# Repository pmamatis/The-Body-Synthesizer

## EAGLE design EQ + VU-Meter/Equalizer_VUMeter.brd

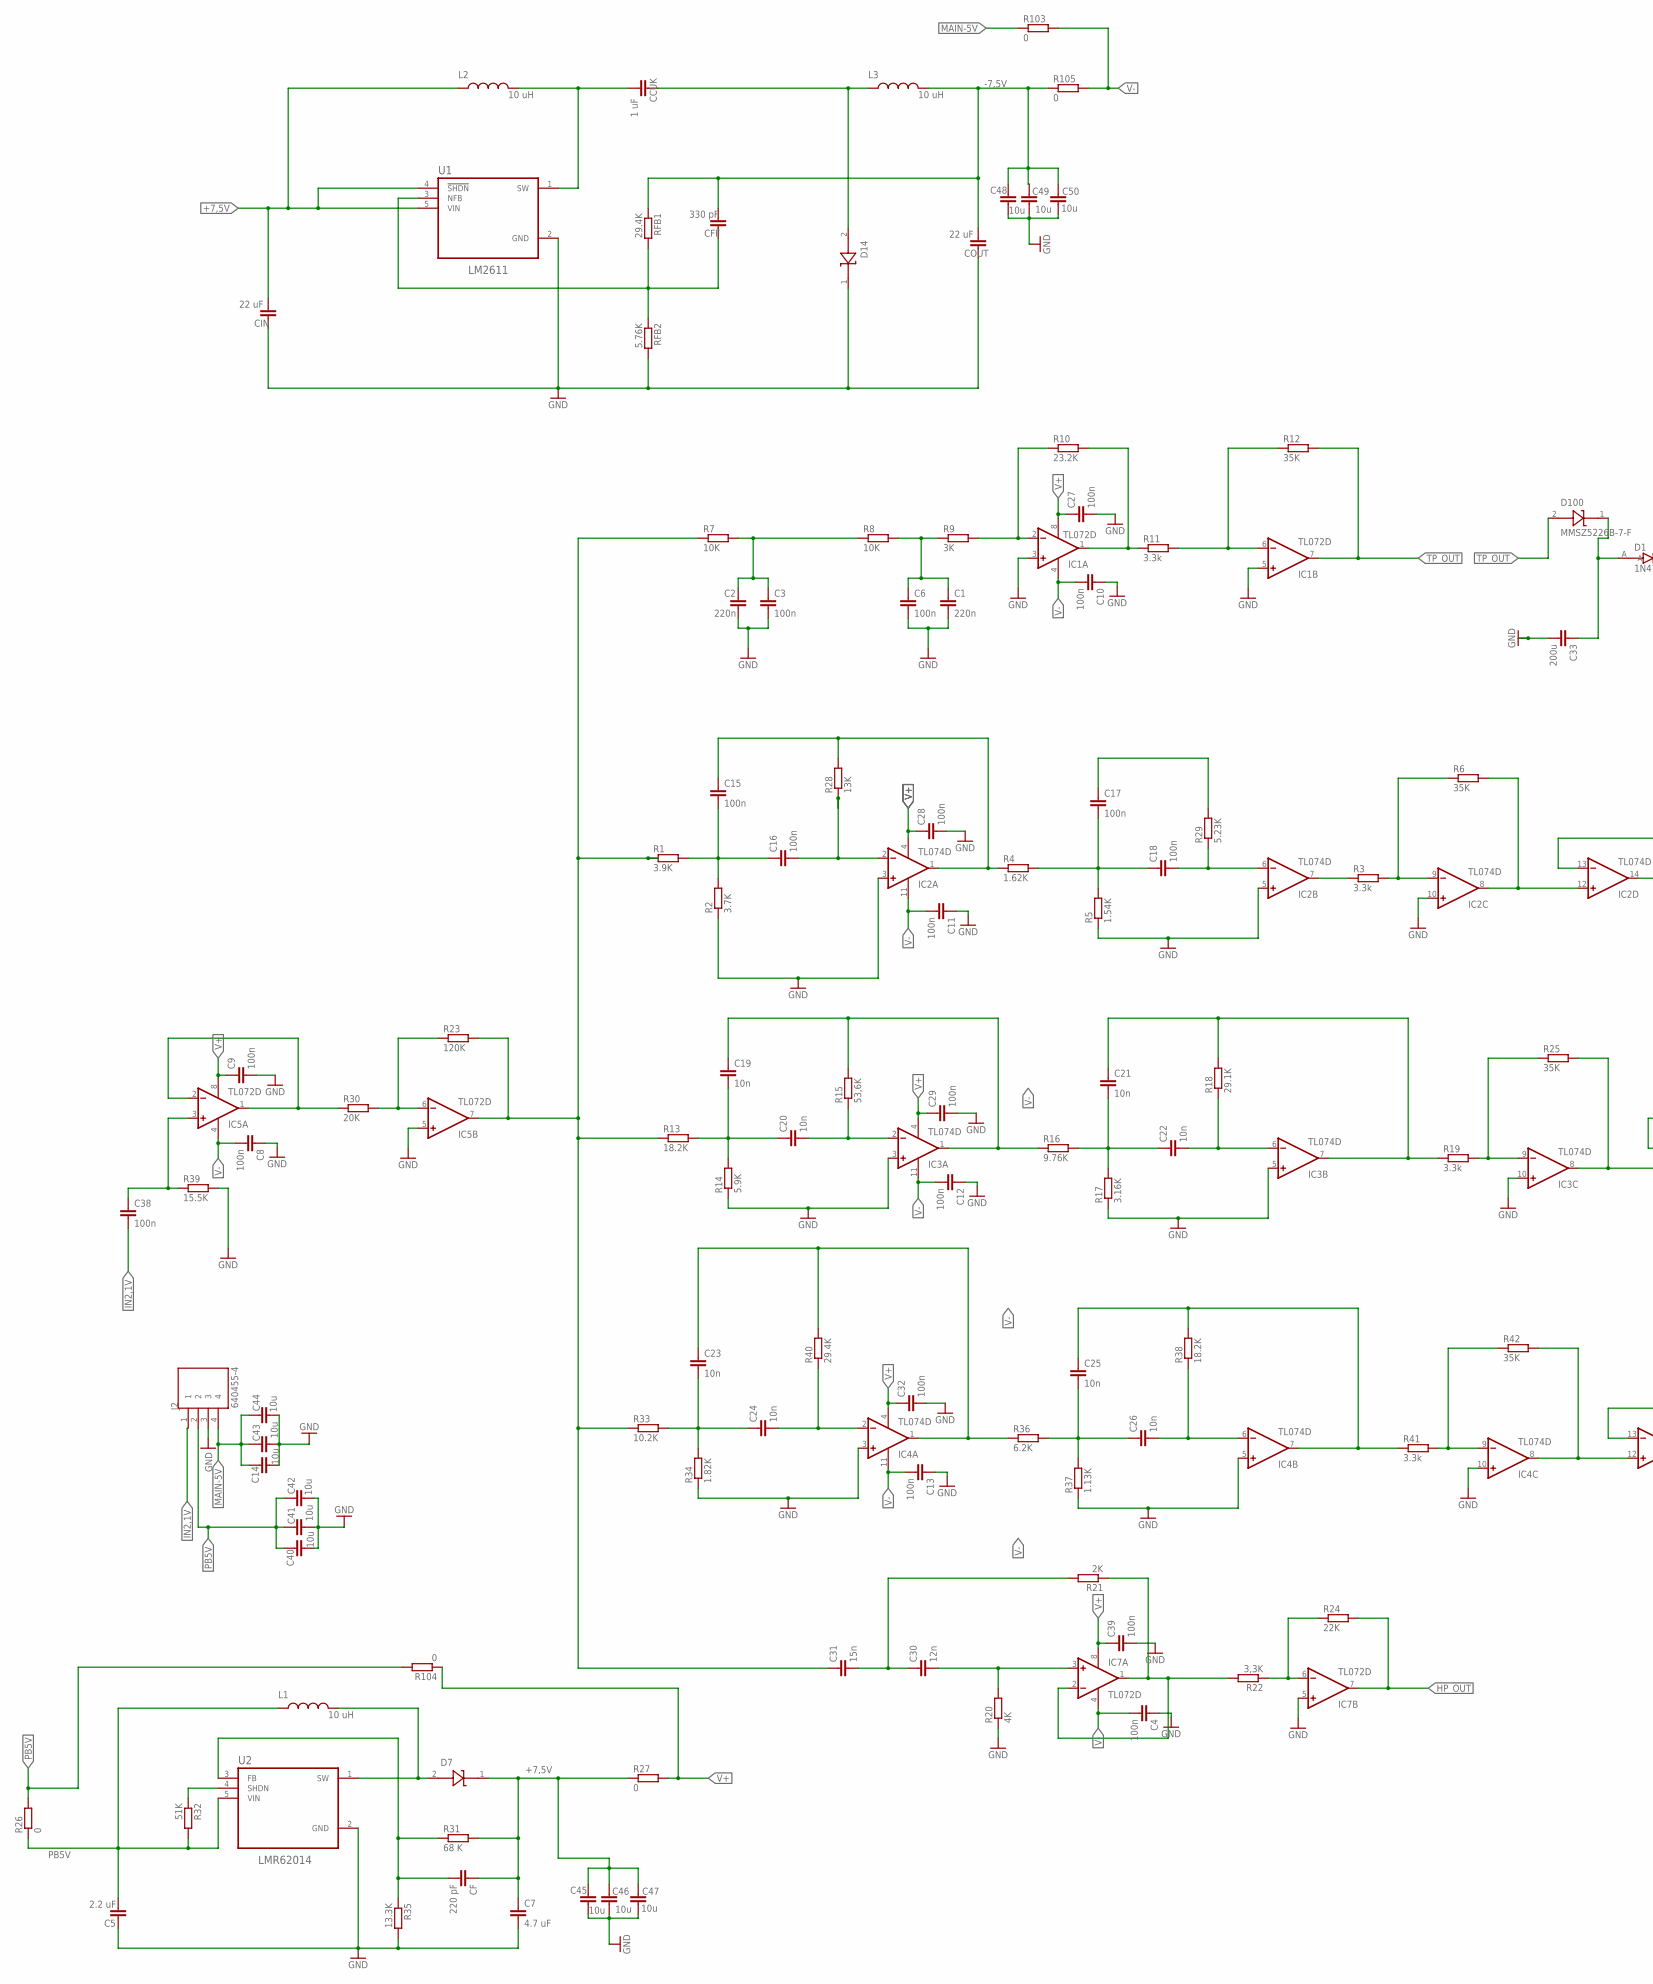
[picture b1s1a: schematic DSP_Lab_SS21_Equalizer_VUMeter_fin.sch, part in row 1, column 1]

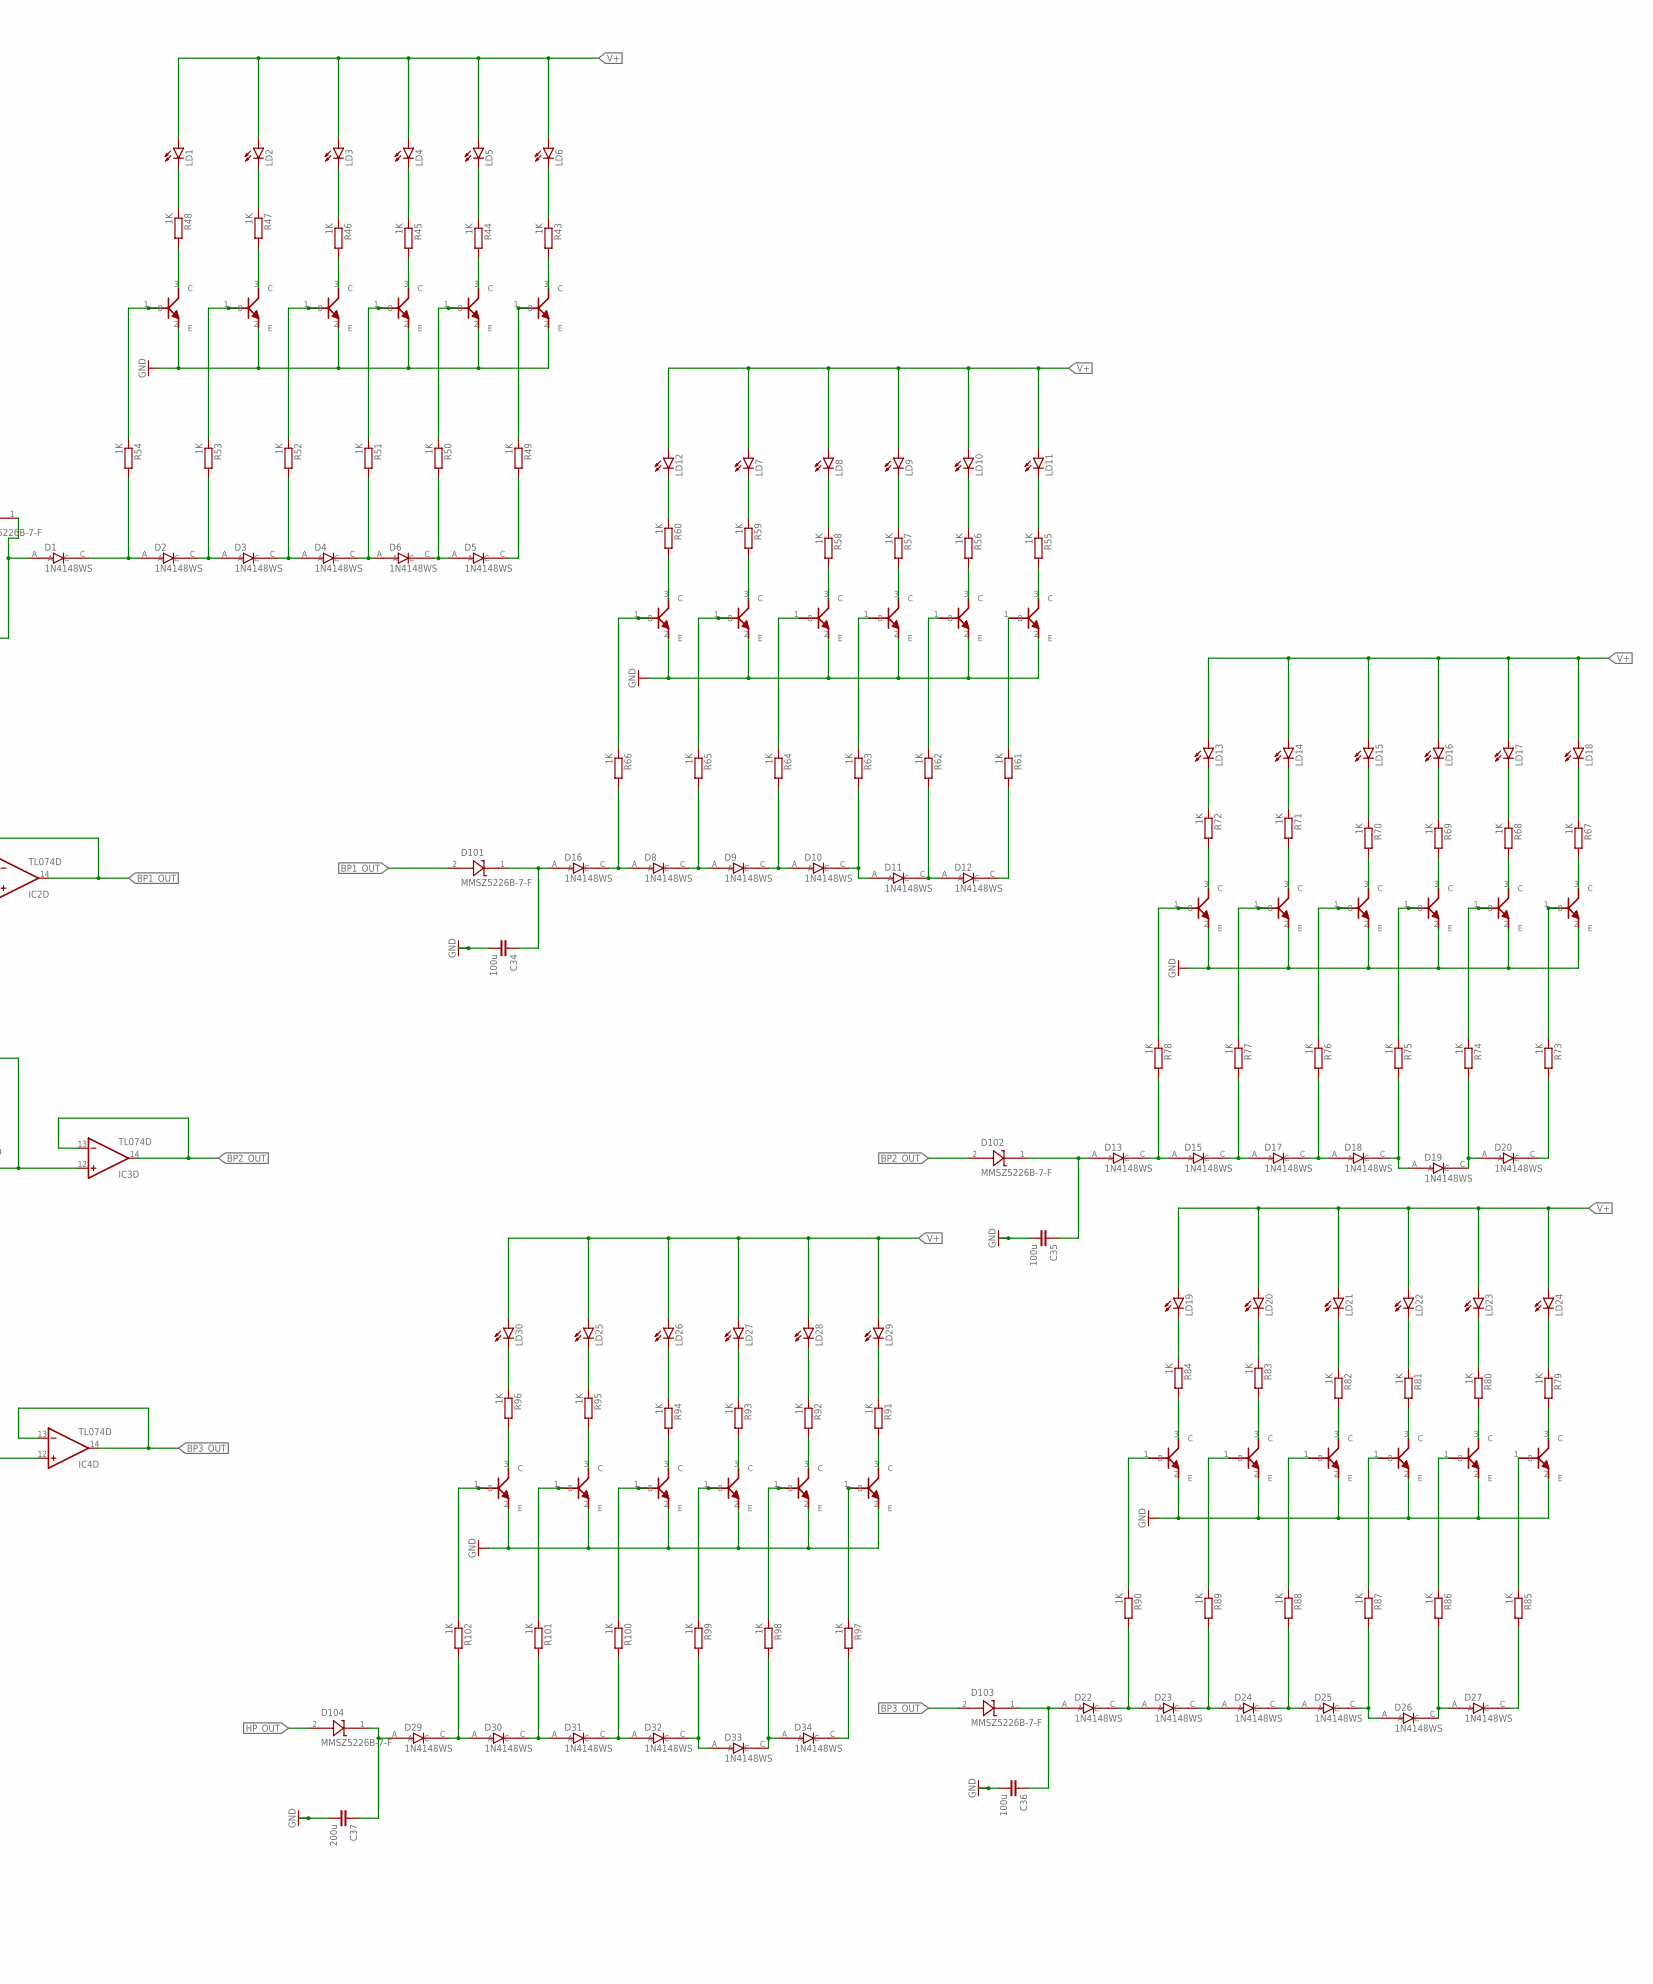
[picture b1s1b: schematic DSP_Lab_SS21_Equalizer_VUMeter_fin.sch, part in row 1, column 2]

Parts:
C1, C2: 220n; C0603
C3, C4, C6, C8, C9, C10, C11, C12, C13, C15, C16, C17, C18, C27, C28, C29, C32, C38, C39: 100n; C0603
C5: 2.2 uF; C0603
C7: 4.7 uF; C0603
C14, C40, C41, C42, C43, C44, C45, C46, C47, C48, C49, C50: 10u; C0603
C19, C20, C21, C22, C23, C24, C25, C26: 10n; C0603
C30: 12n; C0603
C31: 15n; C0603
C33, C37: 200u; C0603
C34, C35, C36: 100u; C0603
CCUK: 1 uF; C0603
CF: 220 pF; C0603
CFF: 330 pF; C0603
CIN: 22 uF; C0603
COUT: 22 uF; C0603
D1, D2, D3, D4, D5, D6, D8, D9, D10, D11, D12, D13, D15, D16, D17, D18, D19, D20, D22, D23, D24, D25, D26, D27, D29, D30, D31, D32, D33, D34: 1N4148WS; SODFL2512X100N
D7, D14, D100, D101, D102, D103, D104: MMSZ5226B-7-F; SOD3715X135L32X57N
IC1, IC5, IC7: TL072D; SO08
IC2, IC3, IC4: TL074D; SO14
J2: 640455-4; TE_640455-4
L1, L2, L3: 10 uH; INDC1608X95N
LD1, LD2, LD3, LD4, LD5, LD6, LD7, LD8, LD9, LD10, LD11, LD12, LD13, LD14, LD15, LD16, LD17, LD18, LD19, LD20, LD21, LD22, LD23, LD24, LD25, LD26, LD27, LD28, LD29, LD30: LEDCHIP-LED0603; CHIP-LED0603
R1: 3.9K; R0603
R2: 3.7K; R0603
R3, R11, R19, R41: 3.3k; R0603
R4: 1.62K; R0603
R5: 1.54K; R0603
R6, R12, R25, R42: 35K; R0603
R7, R8: 10K; R0603
R9: 3K; R0603
R10: 23.2K; R0603
R13, R38: 18.2K; R0603
R14: 5.9K; R0603
R15: 53,6K; R0603
R16: 9.76K; R0603
R17: 3.16K; R0603
R18: 29.1K; R0603
R20: 4K; R0603
R21: 2K; R0603
R22: 3,3K; R0603
R23: 120K; R0603
R24: 22K; R0603
R26, R27, R103, R104, R105: 0; R0603
R28: 13K; R0603
R29: 5.23K; R0603
R30: 20K; R0603
R31: 68 K; R0603
R32: 51K; R0603
R33: 10.2K; R0603
R34: 1.82K; R0603
R35: 13.3K; R0603
R36: 6.2K; R0603
R37: 1.13K; R0603
R39: 15.5K; R0603
R40: 29.4K; R0603
R43, R44, R45, R46, R47, R48, R49, R50, R51, R52, R53, R54, R55, R56, R57, R58, R59, R60, R61, R62, R63, R64, R65, R66, R67, R68, R69, R70, R71, R72, R73, R74, R75, R76, R77, R78, R79, R80, R81, R82, R83, R84, R85, R86, R87, R88, R89, R90, R91, R92, R93, R94, R95, R96, R97, R98, R99, R100, R101, R102: 1K; R0603
RFB1: 29.4K; R0603
RFB2: 5.76K; R0603
T1, T2, T3, T4, T5, T6, T7, T8, T9, T10, T11, T12, T13, T14, T15, T16, T17, T18, T19, T20, T21, T22, T23, T24, T25, T26, T27, T28, T29, T30: BC846A; SOT23-3
U1: LM2611; SOT95P280X145-5N
U2: LMR62014; SOT95P280X145-5N

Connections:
+7,5V: C7.1, C45.2, C46.1, C47.1, CF.1, CIN.1, D7.1 (C), L2.1, R27.1, R31.2, U1.4 (!SHDN), U1.5 (VIN)
-7,5V: C48.2, C49.1, C50.1, CFF.1, COUT.1, L3.2, R105.1, RFB1.1
BP1_OUT: D101.2 (A), IC2.13 (-IN), IC2.14 (OUT)
BP2_OUT: D102.2 (A), IC3.13 (-IN), IC3.14 (OUT)
BP3_OUT: D103.2 (A), IC4.13 (-IN), IC4.14 (OUT)
GND: C1.2, C2.2, C3.2, C4.1, C5.2, C6.2, C7.2, C8.1, C9.2, C10.1, C11.1, C12.1, C13.1, C14.1, C27.2, C28.2, C29.2, C32.2, C33.2, C34.2, C35.2, C36.2, C37.2, C39.2, C40.1, C41.2, C42.2, C43.2, C44.2, C45.1, C46.2, C47.2, C48.1, C49.2, C50.2, CIN.2, COUT.2, D14.1 (C), IC1.3 (+IN), IC1.5 (+IN), IC2.3 (+IN), IC2.5 (+IN), IC2.10 (+IN), IC3.3 (+IN), IC3.5 (+IN), IC3.10 (+IN), IC4.3 (+IN), IC4.5 (+IN), IC4.10 (+IN), IC5.5 (+IN), IC7.5 (+IN), J2.3, R2.1, R5.1, R14.1, R17.1, R20.1, R34.1, R35.2, R37.1, R39.2, RFB2.2, T1.2 (E), T2.2 (E), T3.2 (E), T4.2 (E), T5.2 (E), T6.2 (E), T7.2 (E), T8.2 (E), T9.2 (E), T10.2 (E), T11.2 (E), T12.2 (E), T13.2 (E), T14.2 (E), T15.2 (E), T16.2 (E), T17.2 (E), T18.2 (E), T19.2 (E), T20.2 (E), T21.2 (E), T22.2 (E), T23.2 (E), T24.2 (E), T25.2 (E), T26.2 (E), T27.2 (E), T28.2 (E), T29.2 (E), T30.2 (E), U1.2 (GND), U2.2 (GND)
HP_OUT: D104.2 (A), IC7.7 (OUT), R24.2
IN2,1V: C38.2, J2.1
MAIN-5V: C14.2, C43.1, C44.1, J2.4, R103.1
unnamed: C1.1, C6.1, R8.2, R9.1
unnamed: IC1.2 (-IN), R9.2, R10.1
unnamed: C2.1, C3.1, R7.2, R8.1
unnamed: C31.1, IC5.7 (OUT), R1.1, R7.1, R13.1, R23.2, R33.1
unnamed: IC2.9 (-IN), R3.2, R6.1
unnamed: IC1.1 (OUT), R10.2, R11.1
unnamed: IC3.9 (-IN), R19.2, R25.1
unnamed: IC1.6 (-IN), R11.2, R12.1
unnamed: C15.2, C16.1, R1.2, R2.2
unnamed: C16.2, IC2.2 (-IN), R28.1
unnamed: C15.1, IC2.1 (OUT), R4.1, R28.2
unnamed: C19.2, C20.1, R13.2, R14.2
unnamed: C17.1, R29.2
unnamed: C18.2, IC2.6 (-IN), R29.1
unnamed: C21.1, IC3.7 (OUT), R18.2, R19.1
unnamed: C20.2, IC3.2 (-IN), R15.1
unnamed: C19.1, IC3.1 (OUT), R15.2, R16.1
unnamed: R32.1, U2.4 (SHDN)
unnamed: CF.2, R31.1, R35.1, U2.3 (FB)
unnamed: C21.2, C22.1, R16.2, R17.2
unnamed: C22.2, IC3.6 (-IN), R18.1
unnamed: IC4.8 (OUT), IC4.12 (+IN), R42.2
unnamed: C23.1, IC4.1 (OUT), R36.1, R40.2
unnamed: C23.2, C24.1, R33.2, R34.2
unnamed: C24.2, IC4.2 (-IN), R40.1
unnamed: IC5.6 (-IN), R23.1, R30.2
unnamed: D15.C, D17.A, R77.2
unnamed: C25.2, C26.1, R36.2, R37.2
unnamed: C26.2, IC4.6 (-IN), R38.1
unnamed: D17.C, D18.A, R76.2
unnamed: C30.2, IC7.3 (+IN), R20.2
unnamed: C17.2, C18.1, R4.2, R5.2
unnamed: IC7.1 (OUT), IC7.2 (-IN), R21.1, R22.2
unnamed: D23.C, D24.A, R89.2
unnamed: C30.1, C31.2, R21.2
unnamed: IC7.6 (-IN), R22.1, R24.1
unnamed: LD6.C, R43.1
unnamed: LD5.C, R44.1
unnamed: IC5.1 (OUT), IC5.2 (-IN), R30.1
unnamed: LD4.C, R45.1
unnamed: LD3.C, R46.1
unnamed: LD2.C, R47.1
unnamed: LD1.C, R48.1
unnamed: C38.1, IC5.3 (+IN), R39.1
unnamed: C25.1, IC4.7 (OUT), R38.2, R41.1
unnamed: R43.2, T6.3 (C)
unnamed: R44.2, T5.3 (C)
unnamed: R45.2, T4.3 (C)
unnamed: R46.2, T3.3 (C)
unnamed: R47.2, T2.3 (C)
unnamed: R48.2, T1.3 (C)
unnamed: R49.1, T6.1 (B)
unnamed: R50.1, T5.1 (B)
unnamed: R51.1, T4.1 (B)
unnamed: R52.1, T3.1 (B)
unnamed: R53.1, T2.1 (B)
unnamed: R54.1, T1.1 (B)
unnamed: C33.1, D1.A, D100.1 (C)
unnamed: D1.C, D2.A, R54.2
unnamed: D2.C, D3.A, R53.2
unnamed: D3.C, D4.A, R52.2
unnamed: D4.C, D6.A, R51.2
unnamed: D5.A, D6.C, R50.2
unnamed: D5.C, R49.2
unnamed: LD11.C, R55.1
unnamed: LD10.C, R56.1
unnamed: LD9.C, R57.1
unnamed: LD8.C, R58.1
unnamed: LD7.C, R59.1
unnamed: LD12.C, R60.1
unnamed: D7.2 (A), L1.2, U2.1 (SW)
unnamed: R55.2, T7.3 (C)
unnamed: R56.2, T8.3 (C)
unnamed: R57.2, T9.3 (C)
unnamed: R58.2, T10.3 (C)
unnamed: R59.2, T11.3 (C)
unnamed: R60.2, T12.3 (C)
unnamed: R61.1, T7.1 (B)
unnamed: R62.1, T8.1 (B)
unnamed: R63.1, T9.1 (B)
unnamed: R64.1, T10.1 (B)
unnamed: R65.1, T11.1 (B)
unnamed: R66.1, T12.1 (B)
unnamed: C34.1, D16.A, D101.1 (C)
unnamed: D8.A, D16.C, R66.2
unnamed: D8.C, D9.A, R65.2
unnamed: D9.C, D10.A, R64.2
unnamed: D10.C, D11.A, R63.2
unnamed: D11.C, D12.A, R62.2
unnamed: D12.C, R61.2
unnamed: LD18.C, R67.1
unnamed: LD17.C, R68.1
unnamed: LD16.C, R69.1
unnamed: LD15.C, R70.1
unnamed: LD14.C, R71.1
unnamed: LD13.C, R72.1
unnamed: IC3.8 (OUT), IC3.12 (+IN), R25.2
unnamed: R67.2, T18.3 (C)
unnamed: R68.2, T17.3 (C)
unnamed: R69.2, T16.3 (C)
unnamed: R70.2, T15.3 (C)
unnamed: R71.2, T14.3 (C)
unnamed: R72.2, T13.3 (C)
unnamed: R73.1, T18.1 (B)
unnamed: R74.1, T17.1 (B)
unnamed: R75.1, T16.1 (B)
unnamed: R76.1, T15.1 (B)
unnamed: R77.1, T14.1 (B)
unnamed: R78.1, T13.1 (B)
unnamed: C35.1, D13.A, D102.1 (C)
unnamed: D13.C, D15.A, R78.2
unnamed: IC2.8 (OUT), IC2.12 (+IN), R6.2
unnamed: D18.C, D19.A, R75.2
unnamed: D19.C, D20.A, R74.2
unnamed: D20.C, R73.2
unnamed: LD24.C, R79.1
unnamed: LD23.C, R80.1
unnamed: LD22.C, R81.1
unnamed: LD21.C, R82.1
unnamed: LD20.C, R83.1
unnamed: LD19.C, R84.1
unnamed: CCUK.2, D14.2 (A), L3.1
unnamed: R79.2, T24.3 (C)
unnamed: R80.2, T23.3 (C)
unnamed: R81.2, T22.3 (C)
unnamed: R82.2, T21.3 (C)
unnamed: R83.2, T20.3 (C)
unnamed: R84.2, T19.3 (C)
unnamed: R85.1, T24.1 (B)
unnamed: R86.1, T23.1 (B)
unnamed: R87.1, T22.1 (B)
unnamed: R88.1, T21.1 (B)
unnamed: R89.1, T20.1 (B)
unnamed: R90.1, T19.1 (B)
unnamed: C36.1, D22.A, D103.1 (C)
unnamed: D22.C, D23.A, R90.2
unnamed: CCUK.1, L2.2, U1.1 (SW)
unnamed: D24.C, D25.A, R88.2
unnamed: D25.C, D26.A, R87.2
unnamed: D26.C, D27.A, R86.2
unnamed: D27.C, R85.2
unnamed: LD29.C, R91.1
unnamed: LD28.C, R92.1
unnamed: LD27.C, R93.1
unnamed: LD26.C, R94.1
unnamed: LD25.C, R95.1
unnamed: LD30.C, R96.1
unnamed: CFF.2, RFB1.2, RFB2.1, U1.3 (NFB)
unnamed: R91.2, T30.3 (C)
unnamed: R92.2, T29.3 (C)
unnamed: R93.2, T28.3 (C)
unnamed: R94.2, T27.3 (C)
unnamed: R95.2, T26.3 (C)
unnamed: R96.2, T25.3 (C)
unnamed: R97.1, T30.1 (B)
unnamed: R98.1, T29.1 (B)
unnamed: R99.1, T28.1 (B)
unnamed: R100.1, T27.1 (B)
unnamed: R101.1, T26.1 (B)
unnamed: R102.1, T25.1 (B)
unnamed: C37.1, D29.A, D104.1 (C)
unnamed: D29.C, D30.A, R102.2
unnamed: D30.C, D31.A, R101.2
unnamed: D31.C, D32.A, R100.2
unnamed: D32.C, D33.A, R99.2
unnamed: D33.C, D34.A, R98.2
unnamed: D34.C, R97.2
unnamed: IC2.7 (OUT), R3.1
unnamed: IC4.9 (-IN), R41.2, R42.1
PB5V: C5.1, C40.2, C41.1, C42.1, J2.2, L1.1, R26.1, R26.2, R32.2, R104.2, U2.5 (VIN)
TP_OUT: D100.2 (A), IC1.7 (OUT), R12.2
V+: C9.1, C27.1, C28.1, C29.1, C32.1, C39.1, IC1.8 (V+), IC2.4 (V+), IC3.4 (V+), IC4.4 (V+), IC5.8 (V+), IC7.8 (V+), LD1.A, LD2.A, LD3.A, LD4.A, LD5.A, LD6.A, LD7.A, LD8.A, LD9.A, LD10.A, LD11.A, LD12.A, LD13.A, LD14.A, LD15.A, LD16.A, LD17.A, LD18.A, LD19.A, LD20.A, LD21.A, LD22.A, LD23.A, LD24.A, LD25.A, LD26.A, LD27.A, LD28.A, LD29.A, LD30.A, R27.2, R104.1
V-: C4.2, C8.2, C10.2, C11.2, C12.2, C13.2, IC1.4 (V-), IC2.11 (V-), IC3.11 (V-), IC4.11 (V-), IC5.4 (V-), IC7.4 (V-), R103.2, R105.2

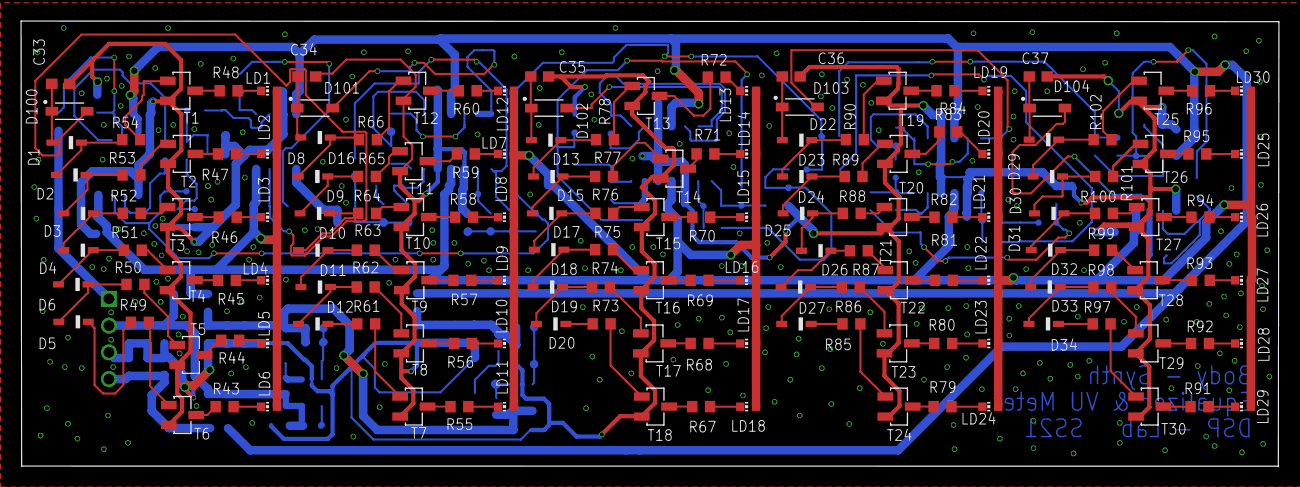
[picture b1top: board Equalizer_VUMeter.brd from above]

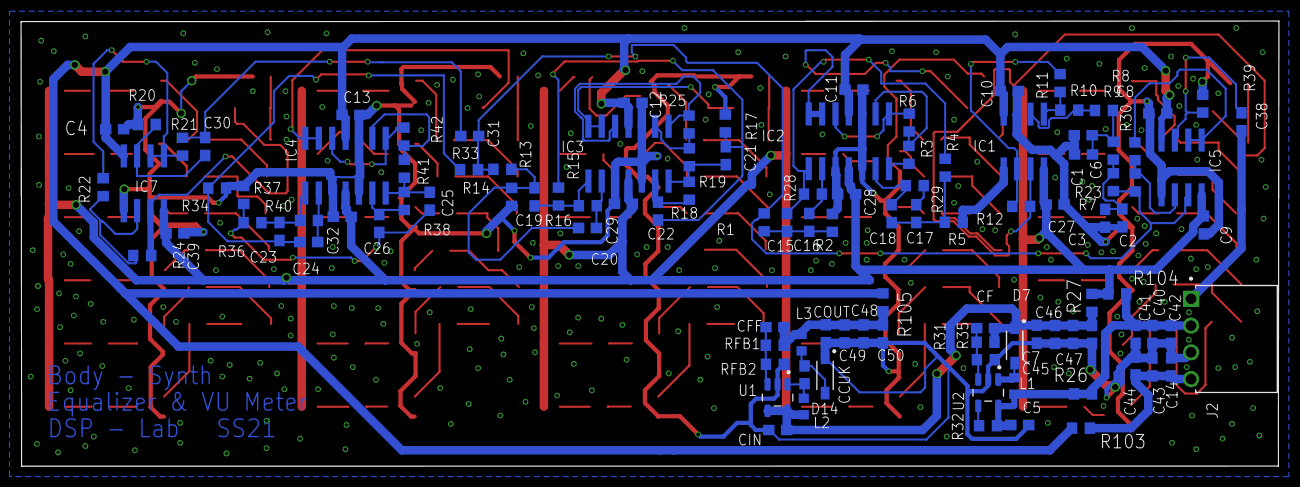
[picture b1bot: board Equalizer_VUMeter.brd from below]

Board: 2 copper layers, 119.5 x 42.3 mm, 271 parts (111 on the bottom side), 182 nets.

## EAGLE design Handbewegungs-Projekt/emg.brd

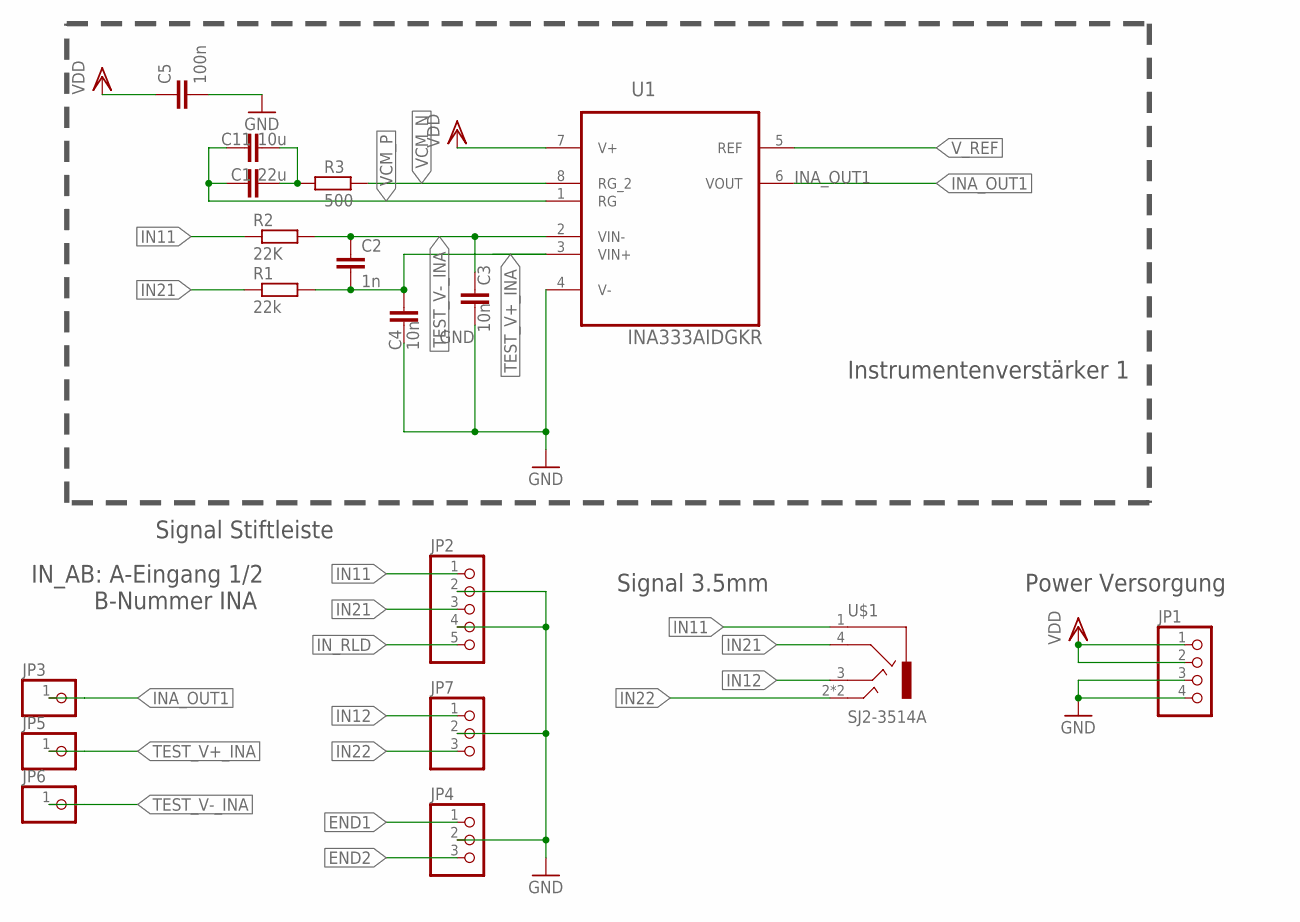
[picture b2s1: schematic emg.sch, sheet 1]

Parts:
C1: 22u; C0805
C2: 1n; C0805
C3, C4: 10n; C0805
C5: 100n; C0805
C11: 10u; C0805
JP1: PINHD-1X4; 1X04
JP2: PINHD-1X5; 1X05
JP3, JP5, JP6: PINHD-1X1; 1X01
JP4, JP7: PINHD-1X3; 1X03
R1: 22k; R0805
R2: 22K; R0805
R3: 500; R0805
U1: INA333AIDGKR; SOP65P490X110-8N
U$1: SJ2-3514A; USR_SJ2-4514A

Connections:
END1: JP4.1; also elsewhere on the board
END2: JP4.3; also elsewhere on the board
GND: C3.2, C4.2, C5.2, JP1.3, JP1.4, JP2.2, JP2.4, JP4.2, JP7.2, U1.4 (V-); also elsewhere on the board
IN11: JP2.1, R2.1, U$1.1
IN12: JP7.1, U$1.3; also elsewhere on the board
IN21: JP2.3, R1.1, U$1.4
IN22: JP7.3, U$1.2, U$1.2_2 (2); also elsewhere on the board
INA_OUT1: JP3.1, U1.6 (VOUT); also elsewhere on the board
IN_RLD: JP2.5; also elsewhere on the board
unnamed: C1.2, C11.2, R3.1
TEST_V+_INA: C2.2, C4.1, JP5.1, R1.2, U1.3 (VIN+)
TEST_V-_INA: C2.1, C3.1, JP6.1, R2.2, U1.2 (VIN-)
VCM_N: R3.2, U1.8 (RG_2); also elsewhere on the board
VCM_P: C1.1, C11.1, U1.1 (RG); also elsewhere on the board
VDD: C5.1, JP1.1, JP1.2, U1.7 (V+); also elsewhere on the board
V_REF: U1.5 (REF); also elsewhere on the board

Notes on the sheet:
Instrumentenverstärker 1
Power Versorgung
Signal 3.5mm
Signal Stiftleiste
IN_AB: A-Eingang 1/2 B-Nummer INA

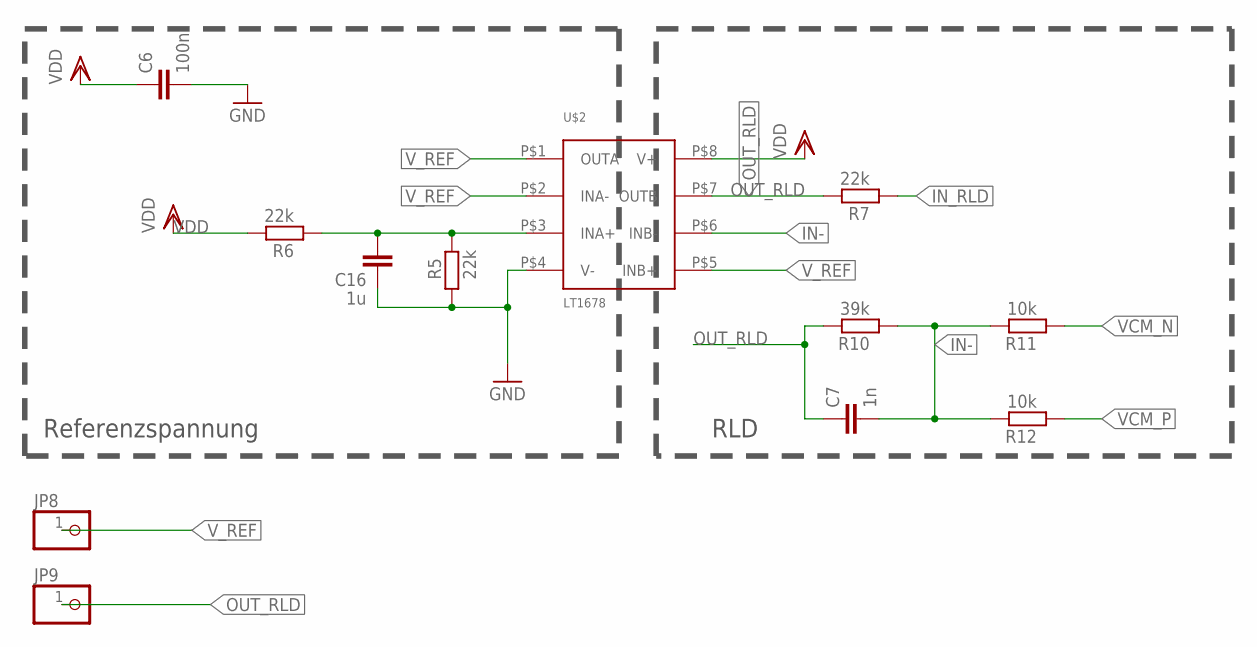
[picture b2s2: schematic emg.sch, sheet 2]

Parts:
C6: 100n; C0805
C7: 1n; C0805
C16: 1u; C0805
JP8, JP9: PINHD-1X1; 1X01
R5, R6, R7: 22k; R0805
R10: 39k; R0805
R11, R12: 10k; R0805
U$2: LT1678; S8

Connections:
GND: C6.2, C16.1, R5.1, U$2.P$4 (V-); also elsewhere on the board
IN-: C7.2, R10.1, R11.2, R12.2, U$2.P$6 (INB-)
IN_RLD: R7.1; also elsewhere on the board
unnamed: C16.2, R5.2, R6.1, U$2.P$3 (INA+)
OUT_RLD: C7.1, JP9.1, R7.2, R10.2, U$2.P$7 (OUTB)
VCM_N: R11.1; also elsewhere on the board
VCM_P: R12.1; also elsewhere on the board
VDD: C6.1, R6.2, U$2.P$8 (V+); also elsewhere on the board
V_REF: JP8.1, U$2.P$1 (OUTA), U$2.P$2 (INA-), U$2.P$5 (INB+); also elsewhere on the board

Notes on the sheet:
Referenzspannung
RLD

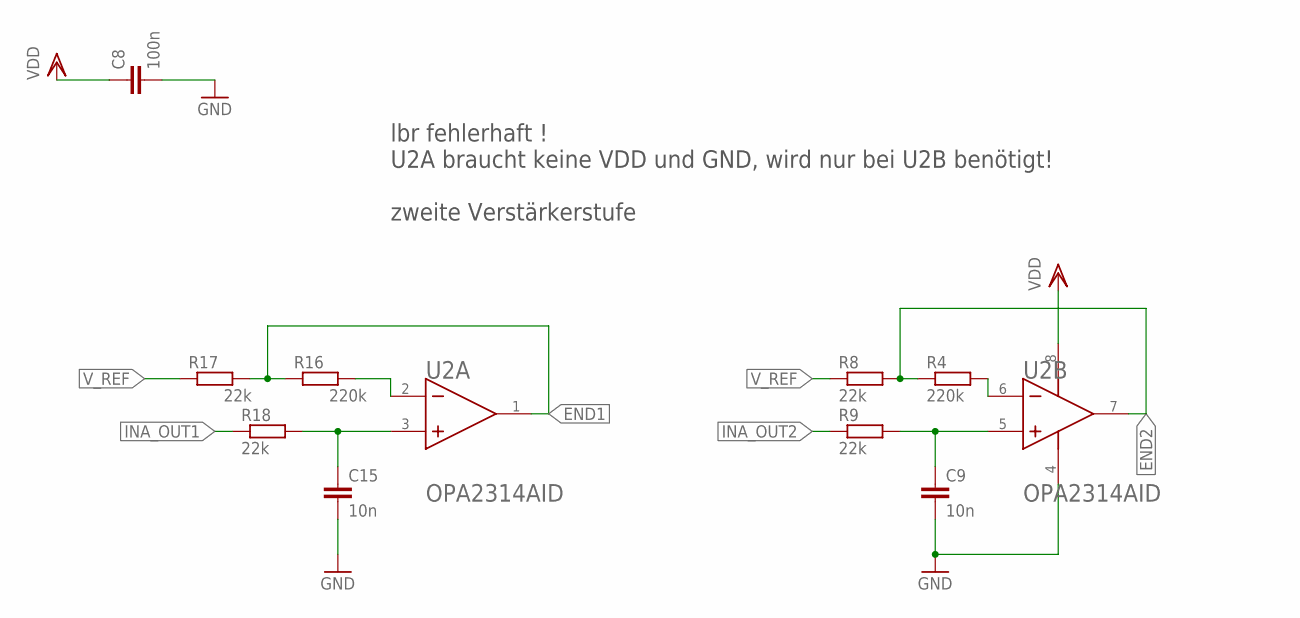
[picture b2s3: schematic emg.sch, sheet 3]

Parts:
C8: 100n; C0805
C9, C15: 10n; C0805
R4, R16: 220k; R0805
R8, R9, R17, R18: 22k; R0805
U2: TEXAS_INSTRUMENTS_OPA2314AIDTEXAS_INSTRUMENTS_OPA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; TEXAS_INSTRUMENTS_OPA2314AID_0

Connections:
END1: R16.1, R17.2, U2.1 (OUT_A); also elsewhere on the board
END2: R4.1, R8.2, U2.7 (OUT_B); also elsewhere on the board
GND: C8.2, C9.2, C15.2, U2.4 (V-); also elsewhere on the board
INA_OUT1: R18.1; also elsewhere on the board
INA_OUT2: R9.1; also elsewhere on the board
unnamed: C9.1, R9.2, U2.5 (IN_B+)
unnamed: R4.2, U2.6 (IN_B-)
unnamed: R16.2, U2.2 (IN_A-)
unnamed: C15.1, R18.2, U2.3 (IN_A+)
VDD: C8.1, U2.8 (V+); also elsewhere on the board
V_REF: R8.1, R17.1; also elsewhere on the board

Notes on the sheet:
lbr fehlerhaft ! U2A braucht keine VDD und GND, wird nur bei U2B benötigt! zweite Verstärkerstufe

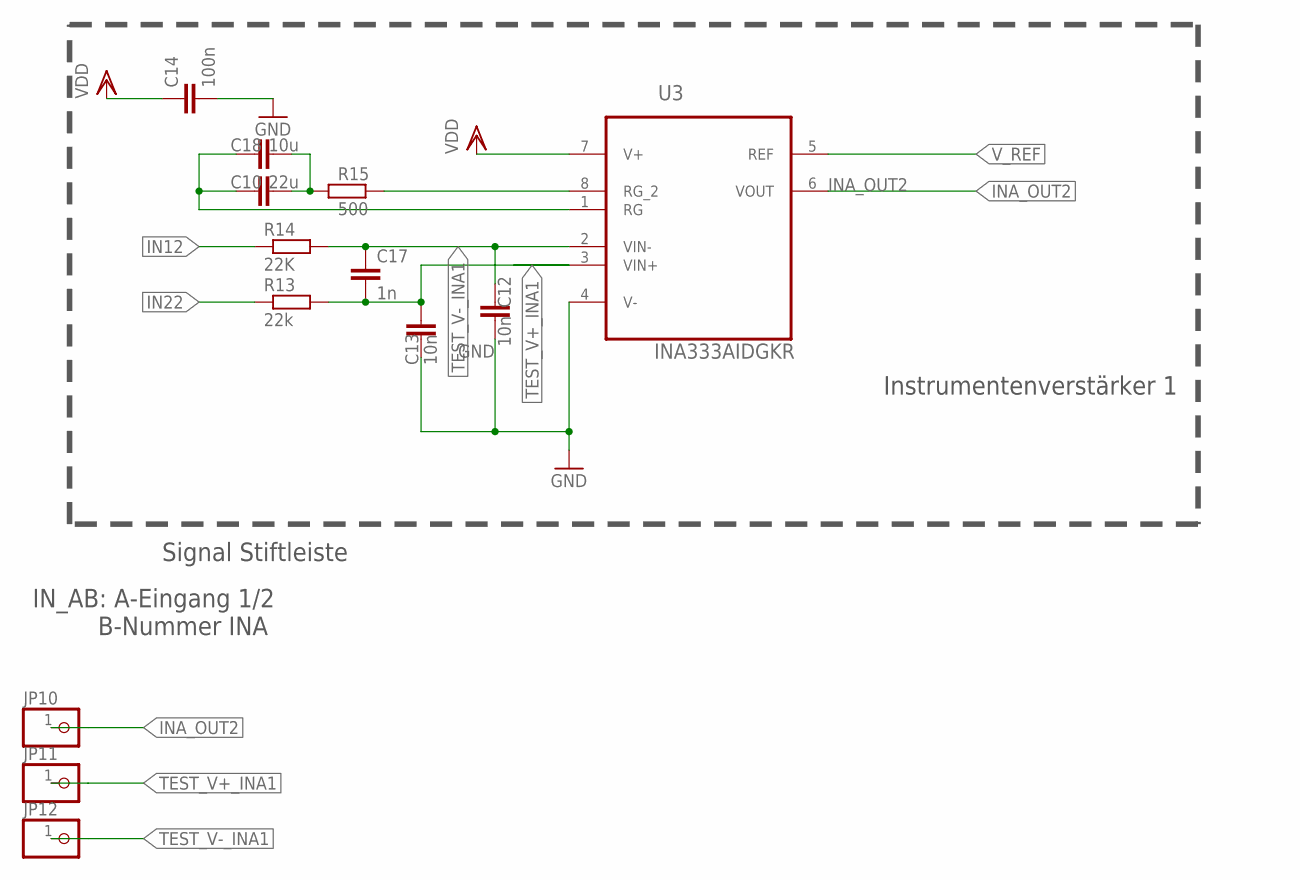
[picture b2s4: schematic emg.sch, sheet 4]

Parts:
C10: 22u; C0805
C12, C13: 10n; C0805
C14: 100n; C0805
C17: 1n; C0805
C18: 10u; C0805
JP10, JP11, JP12: PINHD-1X1; 1X01
R13: 22k; R0805
R14: 22K; R0805
R15: 500; R0805
U3: INA333AIDGKR; SOP65P490X110-8N

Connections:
GND: C12.2, C13.2, C14.2, U3.4 (V-); also elsewhere on the board
IN12: R14.1; also elsewhere on the board
IN22: R13.1; also elsewhere on the board
INA_OUT2: JP10.1, U3.6 (VOUT); also elsewhere on the board
unnamed: C10.2, C18.2, R15.1
unnamed: R15.2, U3.8 (RG_2)
unnamed: C10.1, C18.1, U3.1 (RG)
TEST_V+_INA1: C13.1, C17.2, JP11.1, R13.2, U3.3 (VIN+)
TEST_V-_INA1: C12.1, C17.1, JP12.1, R14.2, U3.2 (VIN-)
VDD: C14.1, U3.7 (V+); also elsewhere on the board
V_REF: U3.5 (REF); also elsewhere on the board

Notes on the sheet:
Instrumentenverstärker 1
Signal Stiftleiste
IN_AB: A-Eingang 1/2 B-Nummer INA

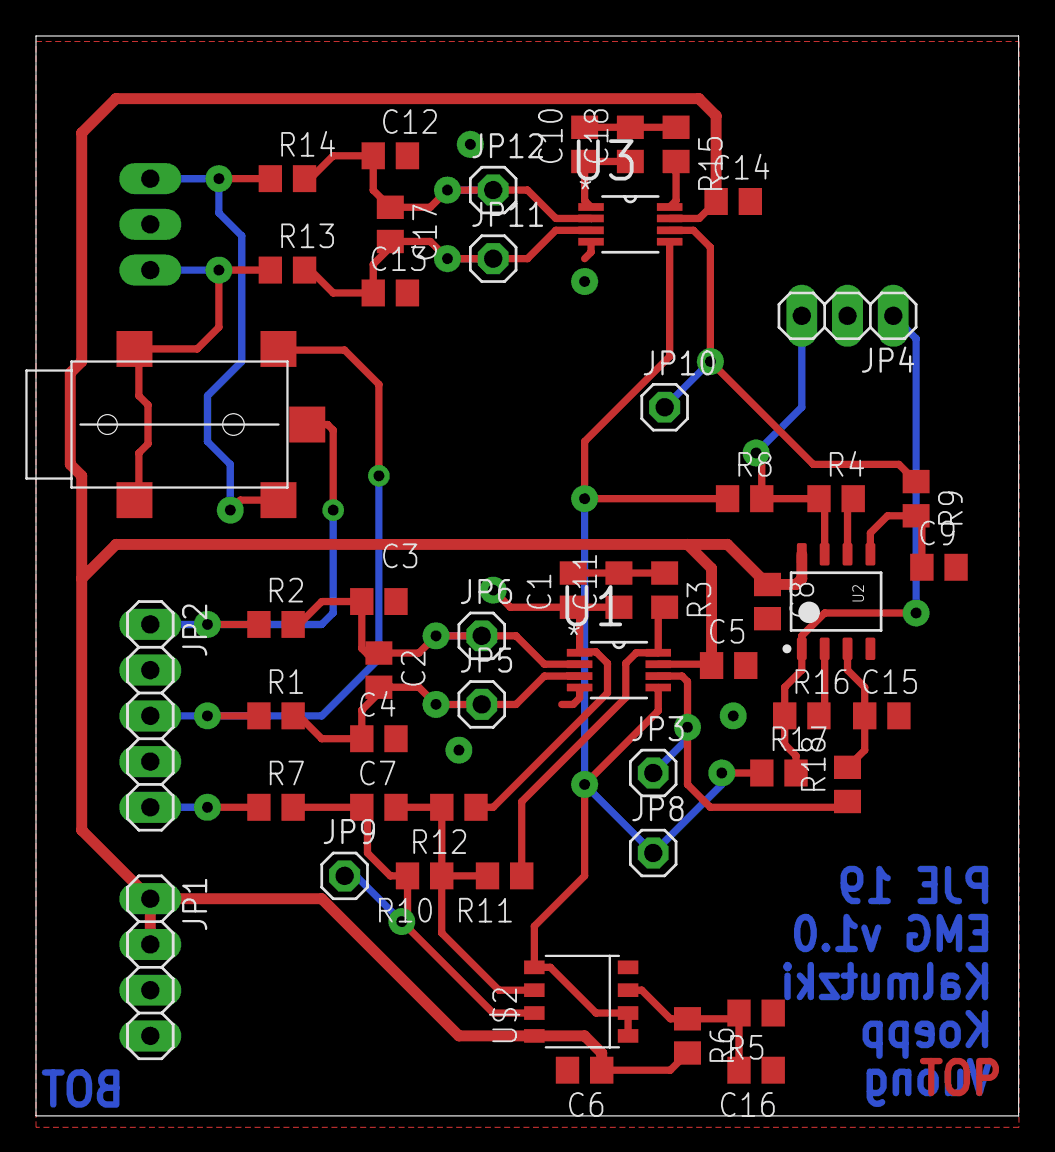
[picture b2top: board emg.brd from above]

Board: 2 copper layers, 54.6 x 60.0 mm, 53 parts (1 on the bottom side), 29 nets.

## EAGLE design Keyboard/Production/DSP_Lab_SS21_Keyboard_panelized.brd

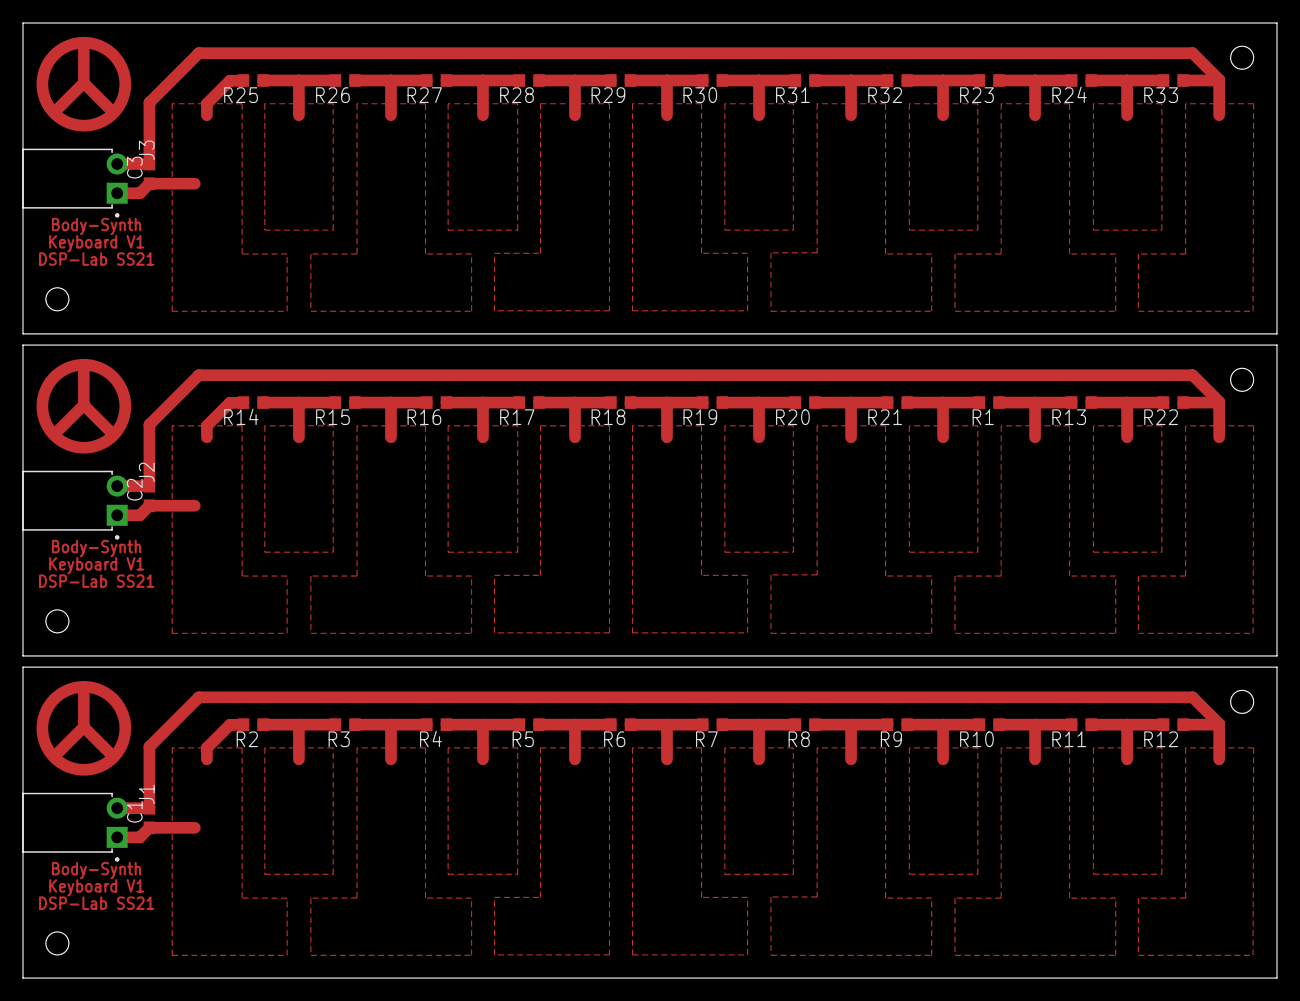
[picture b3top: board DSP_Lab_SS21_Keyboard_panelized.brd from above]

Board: 2 copper layers, 109.0 x 83.0 mm, 39 parts (0 on the bottom side), 36 nets.

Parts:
C1, C2, C3: C0603
J1, J2, J3: 640455-2; TE_640455-2
R1, R2, R3, R4, R5, R6, R7, R8, R9, R10, R11, R12, R13, R14, R15, R16, R17, R18, R19, R20, R21, R22, R23, R24, R25, R26, R27, R28, R29, R30, R31, R32, R33: 2.2k; R0603

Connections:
3V1: C2.2, J2.2, R22.1
3V2: C3.2, J3.2, R33.1
3V3: C1.2, J1.2, R12.1
GND: C1.1, J1.1, R2.2
GND1: C2.1, J2.1, R14.2
GND2: C3.1, J3.1, R25.2
STEP1: R19.1, R20.2
STEP2: R2.1, R3.2
STEP3: R3.1, R4.2
STEP4: R4.1, R5.2
STEP5: R5.1, R6.2
STEP6: R6.1, R7.2
STEP7: R7.1, R8.2
STEP8: R8.1, R9.2
STEP9: R9.1, R10.2
STEP10: R10.1, R11.2
STEP11: R11.1, R12.2
STEP12: R14.1, R15.2
STEP13: R15.1, R16.2
STEP14: R16.1, R17.2
STEP15: R17.1, R18.2
STEP16: R18.1, R19.2
STEP17: R20.1, R21.2
STEP18: R1.2, R21.1
STEP19: R1.1, R13.2
STEP20: R13.1, R22.2
STEP21: R30.1, R31.2
STEP22: R25.1, R26.2
STEP23: R26.1, R27.2
STEP24: R27.1, R28.2
STEP25: R28.1, R29.2
STEP26: R29.1, R30.2
STEP27: R31.1, R32.2
STEP28: R23.2, R32.1
STEP29: R23.1, R24.2
STEP30: R24.1, R33.2
